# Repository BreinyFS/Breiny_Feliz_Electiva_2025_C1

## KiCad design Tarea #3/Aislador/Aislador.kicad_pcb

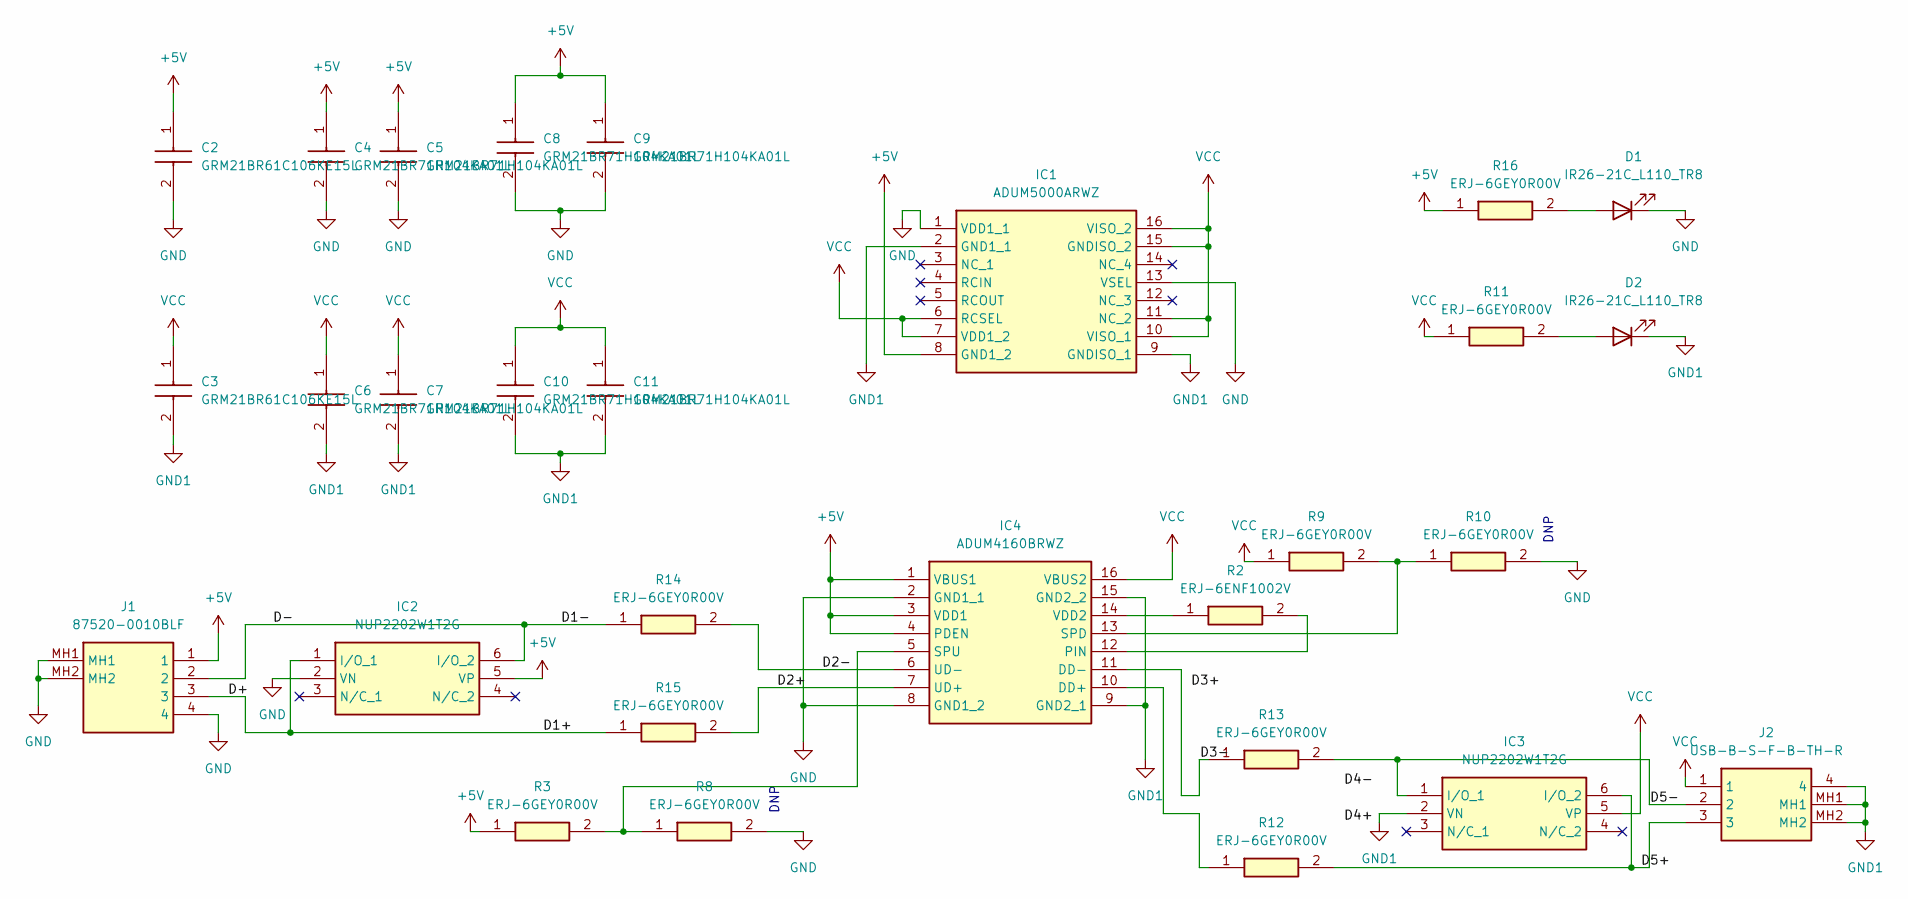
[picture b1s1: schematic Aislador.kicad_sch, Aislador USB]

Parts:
C2, C3: GRM21BR61C106KE15L; CAPC2012X145N; Manufacturer_Part_Number GRM21BR61C106KE15L; Mouser Part Number 81-GRM21BR61C106KE15
C4, C5, C6, C7, C8, C9, C10, C11: GRM21BR71H104KA01L; CAPC2012X145N; Manufacturer_Part_Number GRM21BR71H104KA01L; Mouser Part Number 81-GRM40X104K50L
D1, D2: IR26-21C_L110_TR8; LED_1206_3216Metric
IC1: ADUM5000ARWZ; SOIC127P1032X265-16N; Manufacturer_Part_Number ADUM5000ARWZ; Mouser Part Number 584-ADUM5000ARWZ
IC2, IC3: NUP2202W1T2G; SOT65P210X110-6N; Manufacturer_Part_Number NUP2202W1T2G; Mouser Part Number 863-NUP2202W1T2G
IC4: ADUM4160BRWZ; SOIC127P1032X265-16N; Manufacturer_Part_Number ADUM4160BRWZ; Mouser Part Number 584-ADUM4160BRWZ
J1: 87520-0010BLF; 875200010BLF; Manufacturer_Part_Number 87520-0010BLF
J2: USB-B-S-F-B-TH-R; USBBSFBTHR; Manufacturer_Part_Number USB-B-S-F-B-TH-R; Mouser Part Number 200-USBBSFBTHR
R2: ERJ-6ENF1002V; ERJ6ENF1000V; Manufacturer_Part_Number ERJ-6ENF1002V; Mouser Part Number 667-ERJ-6ENF1002V
R3, R8, R9, R10, R11, R12, R13, R14, R15, R16: ERJ-6GEY0R00V; RESC2012X70N; Manufacturer_Part_Number ERJ-6GEY0R00V; Mouser Part Number 667-ERJ-6GEY0R00V

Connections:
+5V: C2.1, C4.1, C5.1, C8.1, C9.1, IC1.8 (GND1_2), IC2.5 (VP), IC4.1 (VBUS1), IC4.3 (VDD1), IC4.4 (PDEN), J1.1, R3.1, R16.1
/D2+: IC4.7 (UD+), R15.2
/D2-: IC4.6 (UD-), R14.2
/D3-: IC4.11 (DD-), R13.1
/D5+: IC3.6 (I/O_2), J2.3, R12.2
/D5-: IC3.1 (I/O_1), J2.2, R13.2
/D+: IC2.1 (I/O_1), J1.3, R15.1
/D-: IC2.6 (I/O_2), J1.2, R14.1
GND: C2.2, C4.2, C5.2, C8.2, C9.2, D1.1 (K), IC1.1 (VDD1_1), IC1.13 (VSEL), IC2.2 (VN), IC4.2 (GND1_1), IC4.8 (GND1_2), J1.4, J1.MH1, J1.MH2, R8.2, R10.2
GND1: C3.2, C6.2, C7.2, C10.2, C11.2, D2.1 (K), IC1.2 (GND1_1), IC1.9 (GNDISO_1), IC3.2 (VN), IC4.9 (GND2_1), IC4.15 (GND2_2), J2.4, J2.MH1, J2.MH2
unnamed: D1.2 (A), R16.2
unnamed: D2.2 (A), R11.2
unnamed: IC4.10 (DD+), R12.1
unnamed: IC4.12 (PIN), R2.2
unnamed: IC4.13 (SPD), R9.2, R10.1
unnamed: IC4.5 (SPU), R3.2, R8.1
unnamed: IC4.14 (VDD2), R2.1
VCC: C3.1, C6.1, C7.1, C10.1, C11.1, IC1.6 (RCSEL), IC1.7 (VDD1_2), IC1.10 (VISO_1), IC1.11 (NC_2), IC1.15 (GNDISO_2), IC1.16 (VISO_2), IC3.5 (VP), IC4.16 (VBUS2), J2.1, R9.1, R11.1

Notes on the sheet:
DNP

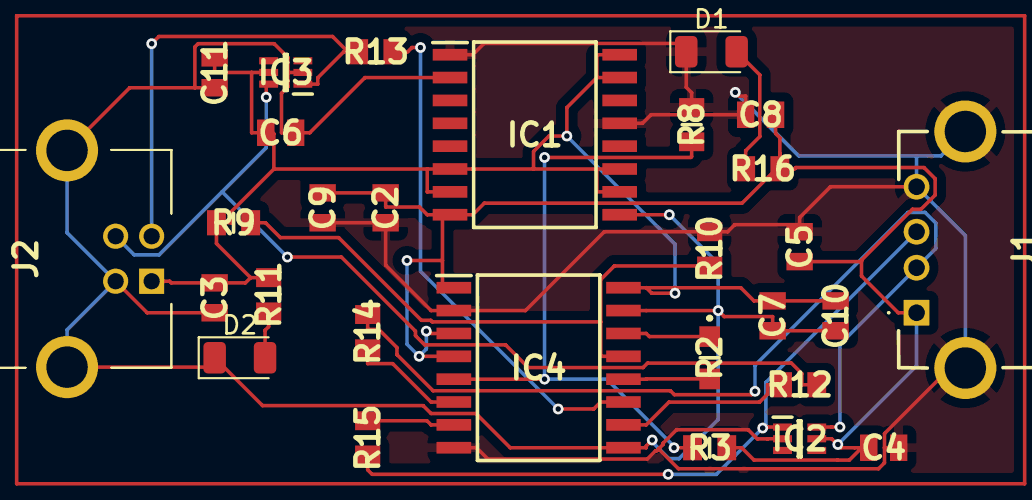
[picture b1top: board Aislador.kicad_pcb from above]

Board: 2 copper layers, 29 parts (0 on the bottom side), 18 nets.

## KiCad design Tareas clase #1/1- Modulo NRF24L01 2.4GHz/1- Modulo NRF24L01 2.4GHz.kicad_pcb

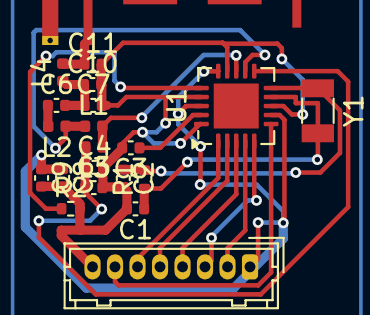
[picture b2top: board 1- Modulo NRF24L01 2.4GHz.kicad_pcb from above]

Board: 2 copper layers, 21 parts (0 on the bottom side), 18 nets.

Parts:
AE1: Antenna; Texas_SWRA117D_2.4GHz_Right
C1, C2: 22pF; C_0402_1005Metric
C3: 33nF; C_0402_1005Metric
C4: 2.2nF; C_0402_1005Metric
C5: 4.7pF; C_0402_1005Metric
C6: 1.5nF; C_0402_1005Metric
C7: 1pF; C_0402_1005Metric
C8: 10nF; C_0402_1005Metric
C9: 1nF; C_0402_1005Metric
C10, C11: Cx; C_0402_1005Metric
J1: Conn_01x08_Pin; Hirose_DF13-08P-1.25DSA_1x08_P1.25mm_Vertical
L1: 8.2nH; L_0402_1005Metric
L2: 3.9nH; L_0402_1005Metric
L3: 2.7nH; L_0402_1005Metric
L4: Lx; L_0402_1005Metric
R1: 10M; R_0402_1005Metric
R2: 22k; R_0402_1005Metric
U1: NRF24L01; QFN-20-1EP_4x4mm_P0.5mm_EP2.5x2.5mm
Y1: 16MHz; Crystal_SMD_3215-2Pin_3.2x1.5mm

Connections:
GND: C1.2, C2.2, C3.2, C4.2, C5.2, C7.2, C8.2, C9.2, C10.2, C11.2, J1.8, R2.2, U1.8 (VSS), U1.14 (VSS), U1.17 (VSS), U1.20 (VSS)
unnamed: AE1.1 (A), C11.1, L4.2
unnamed: C6.1, L2.2
unnamed: C6.2, C7.1, C10.1, L4.1
unnamed: J1.2, U1.4 (MOSI)
unnamed: J1.3, U1.5 (MISO)
unnamed: J1.4, U1.3 (SCK)
unnamed: J1.5, U1.2 (CSN)
unnamed: J1.6, U1.1 (CE)
unnamed: J1.7, U1.6 (IRQ)
unnamed: L1.1, L2.1, U1.12 (ANT1)
unnamed: L1.2, L3.1, U1.13 (ANT2)
unnamed: C3.1, U1.19 (DVDD)
unnamed: R2.1, U1.16 (IREF)
unnamed: C4.1, C5.1, L3.2, U1.11 (VDD_PA)
unnamed: C2.1, R1.2, U1.10 (XC1), Y1.2
unnamed: C1.1, R1.1, U1.9 (XC2), Y1.1
VCC: C8.1, C9.1, J1.1, U1.7 (VDD), U1.15 (VDD), U1.18 (VDD)

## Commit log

2025-01-21 1- Modulo NRF24L01 2.4GHz
2025-01-22 Resumen
2025-03-13 Create DOC - Plantilla Para Desarrollo de Producto Basada Norma IEEE-830 STD - Breiny Feliz.docx
    Plantilla de desarrollo
2025-03-13 Update DOC - Plantilla Para Desarrollo de Producto Basada Norma IEEE-830 STD - Breiny Feliz.docx
    Parte #1
2025-03-14 Update DOC - Plantilla Para Desarrollo de Producto Basada Norma IEEE-830 STD - Breiny Feliz.docx
    Parte #2
2025-03-19 Update DOC - Plantilla Para Desarrollo de Producto Basada Norma IEEE-830 STD - Breiny Feliz.docx
    Parte 3 y 4 completadas
2025-03-19 Tarea #3
    Aislador
2025-03-19 Aislador
2025-03-19 Tarea #3
2025-03-21 Libreria
2025-04-19 Tarea Final
